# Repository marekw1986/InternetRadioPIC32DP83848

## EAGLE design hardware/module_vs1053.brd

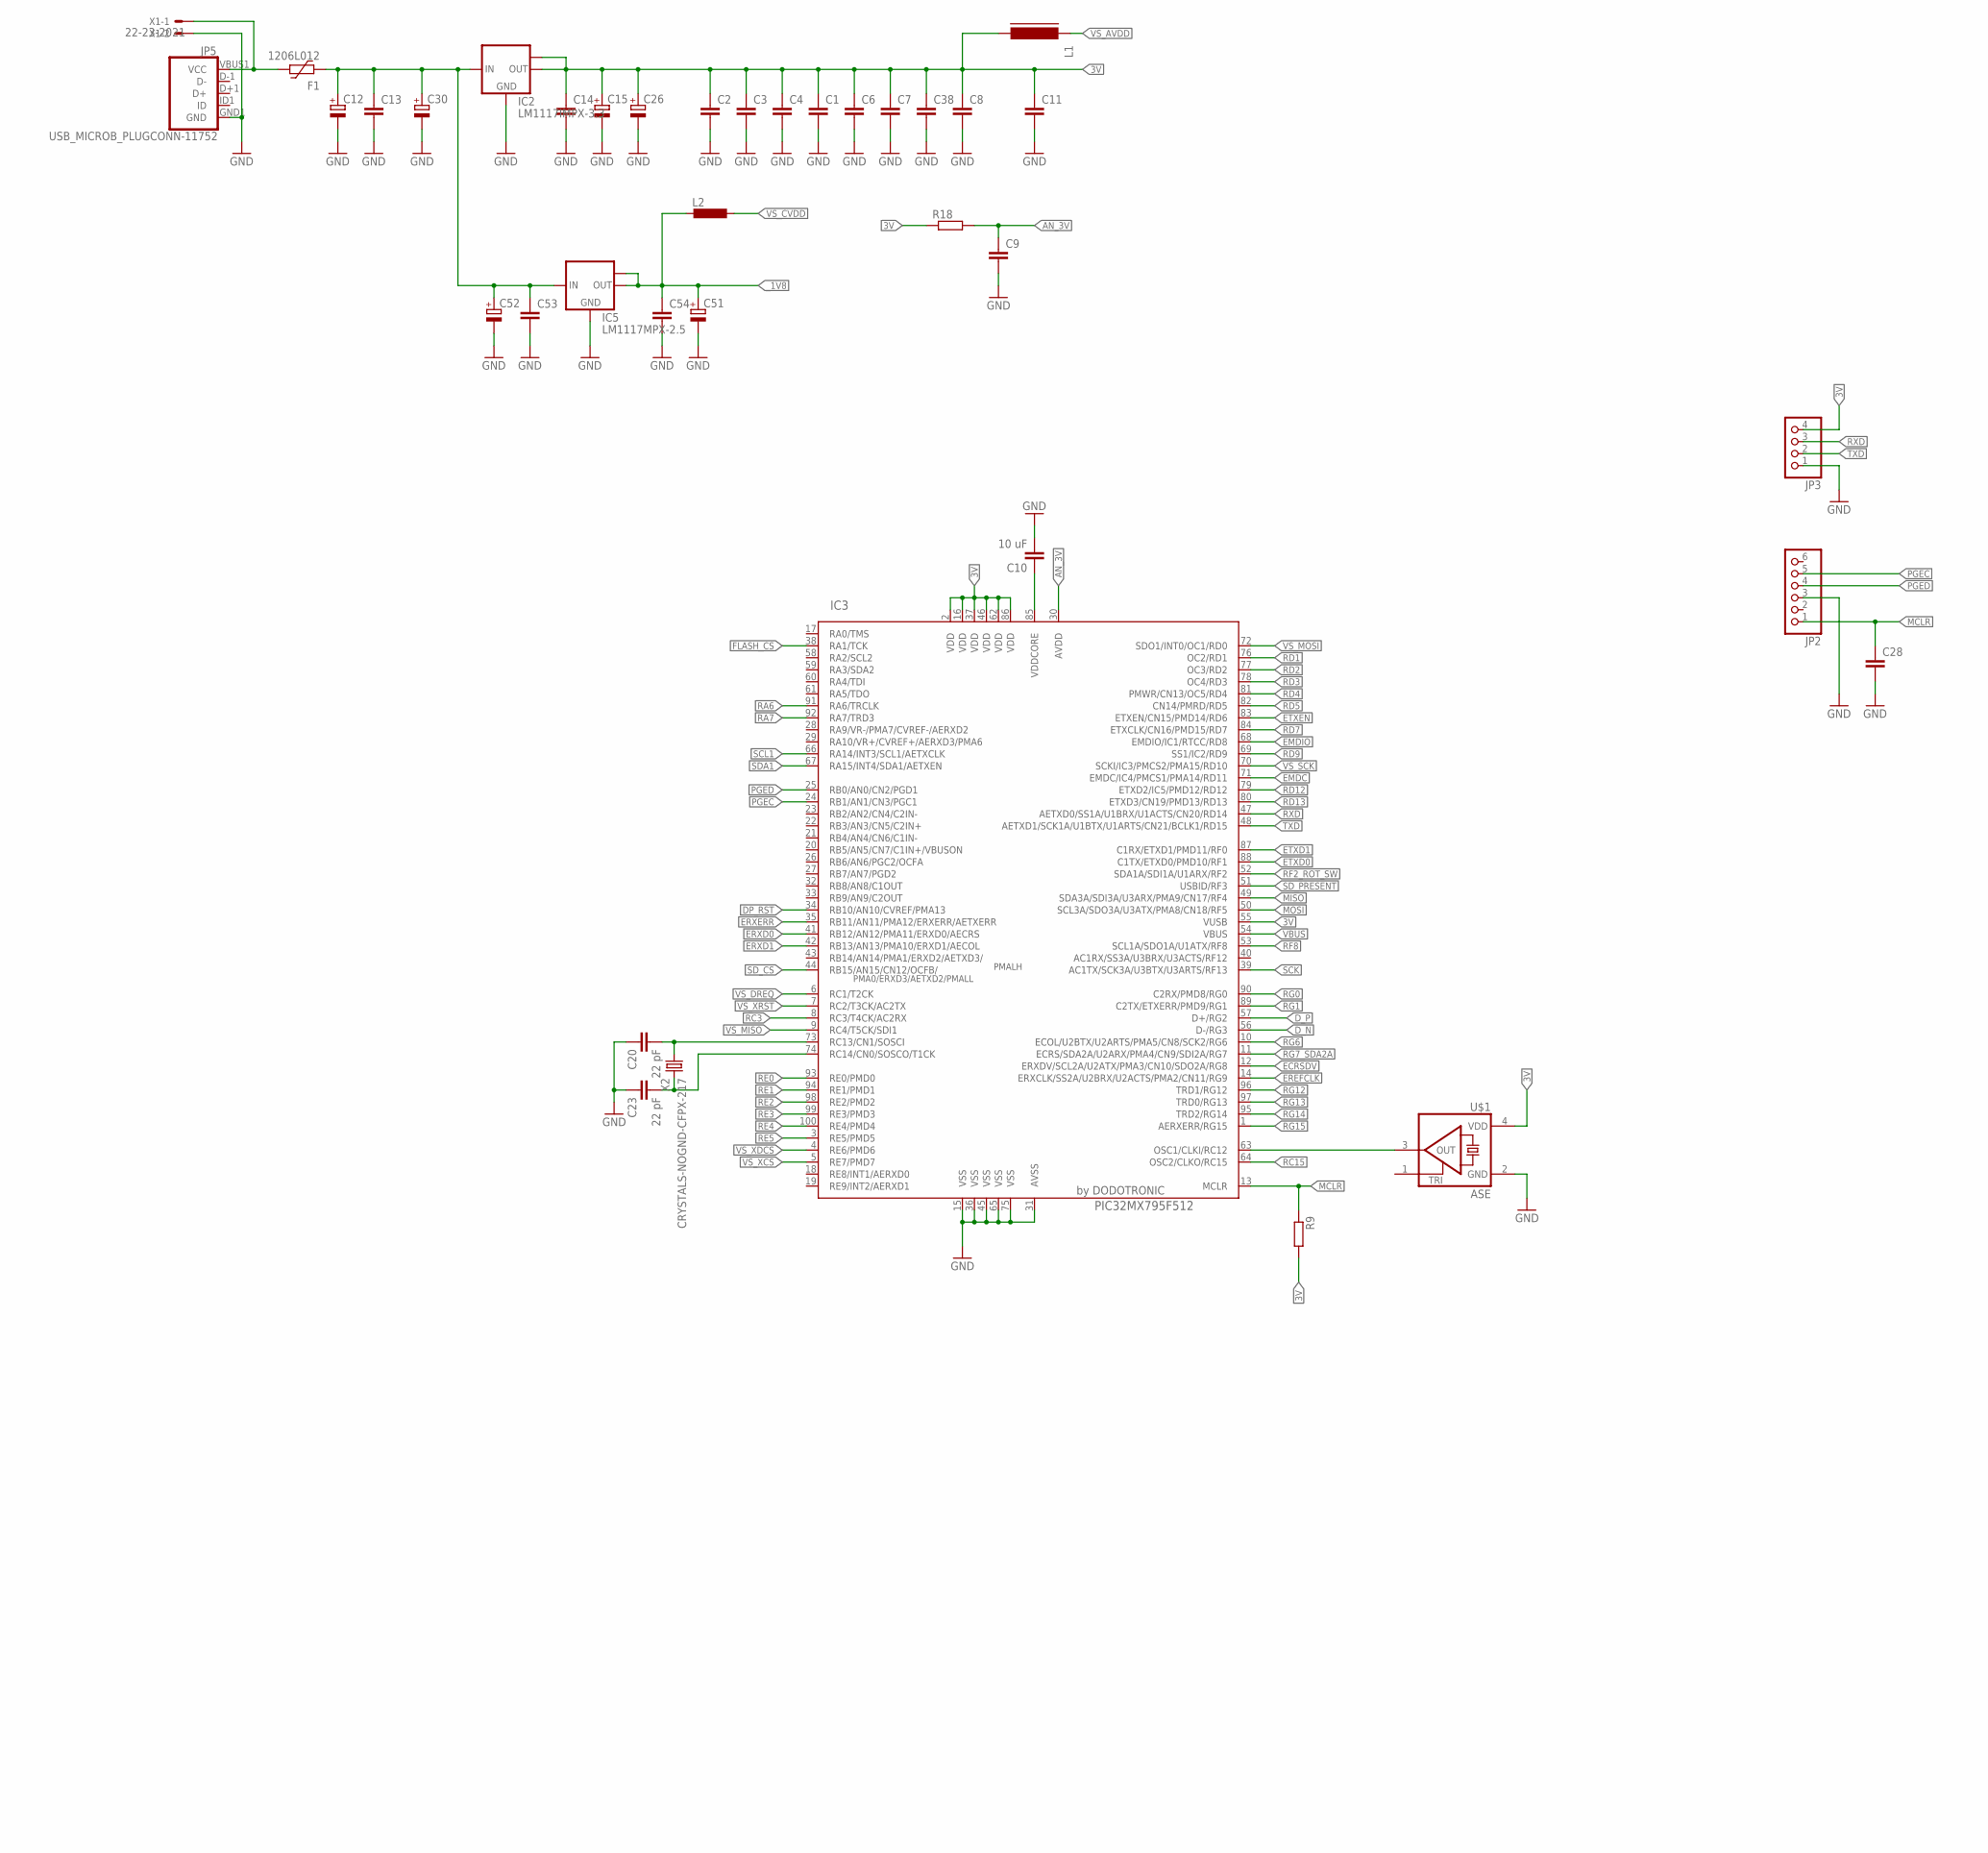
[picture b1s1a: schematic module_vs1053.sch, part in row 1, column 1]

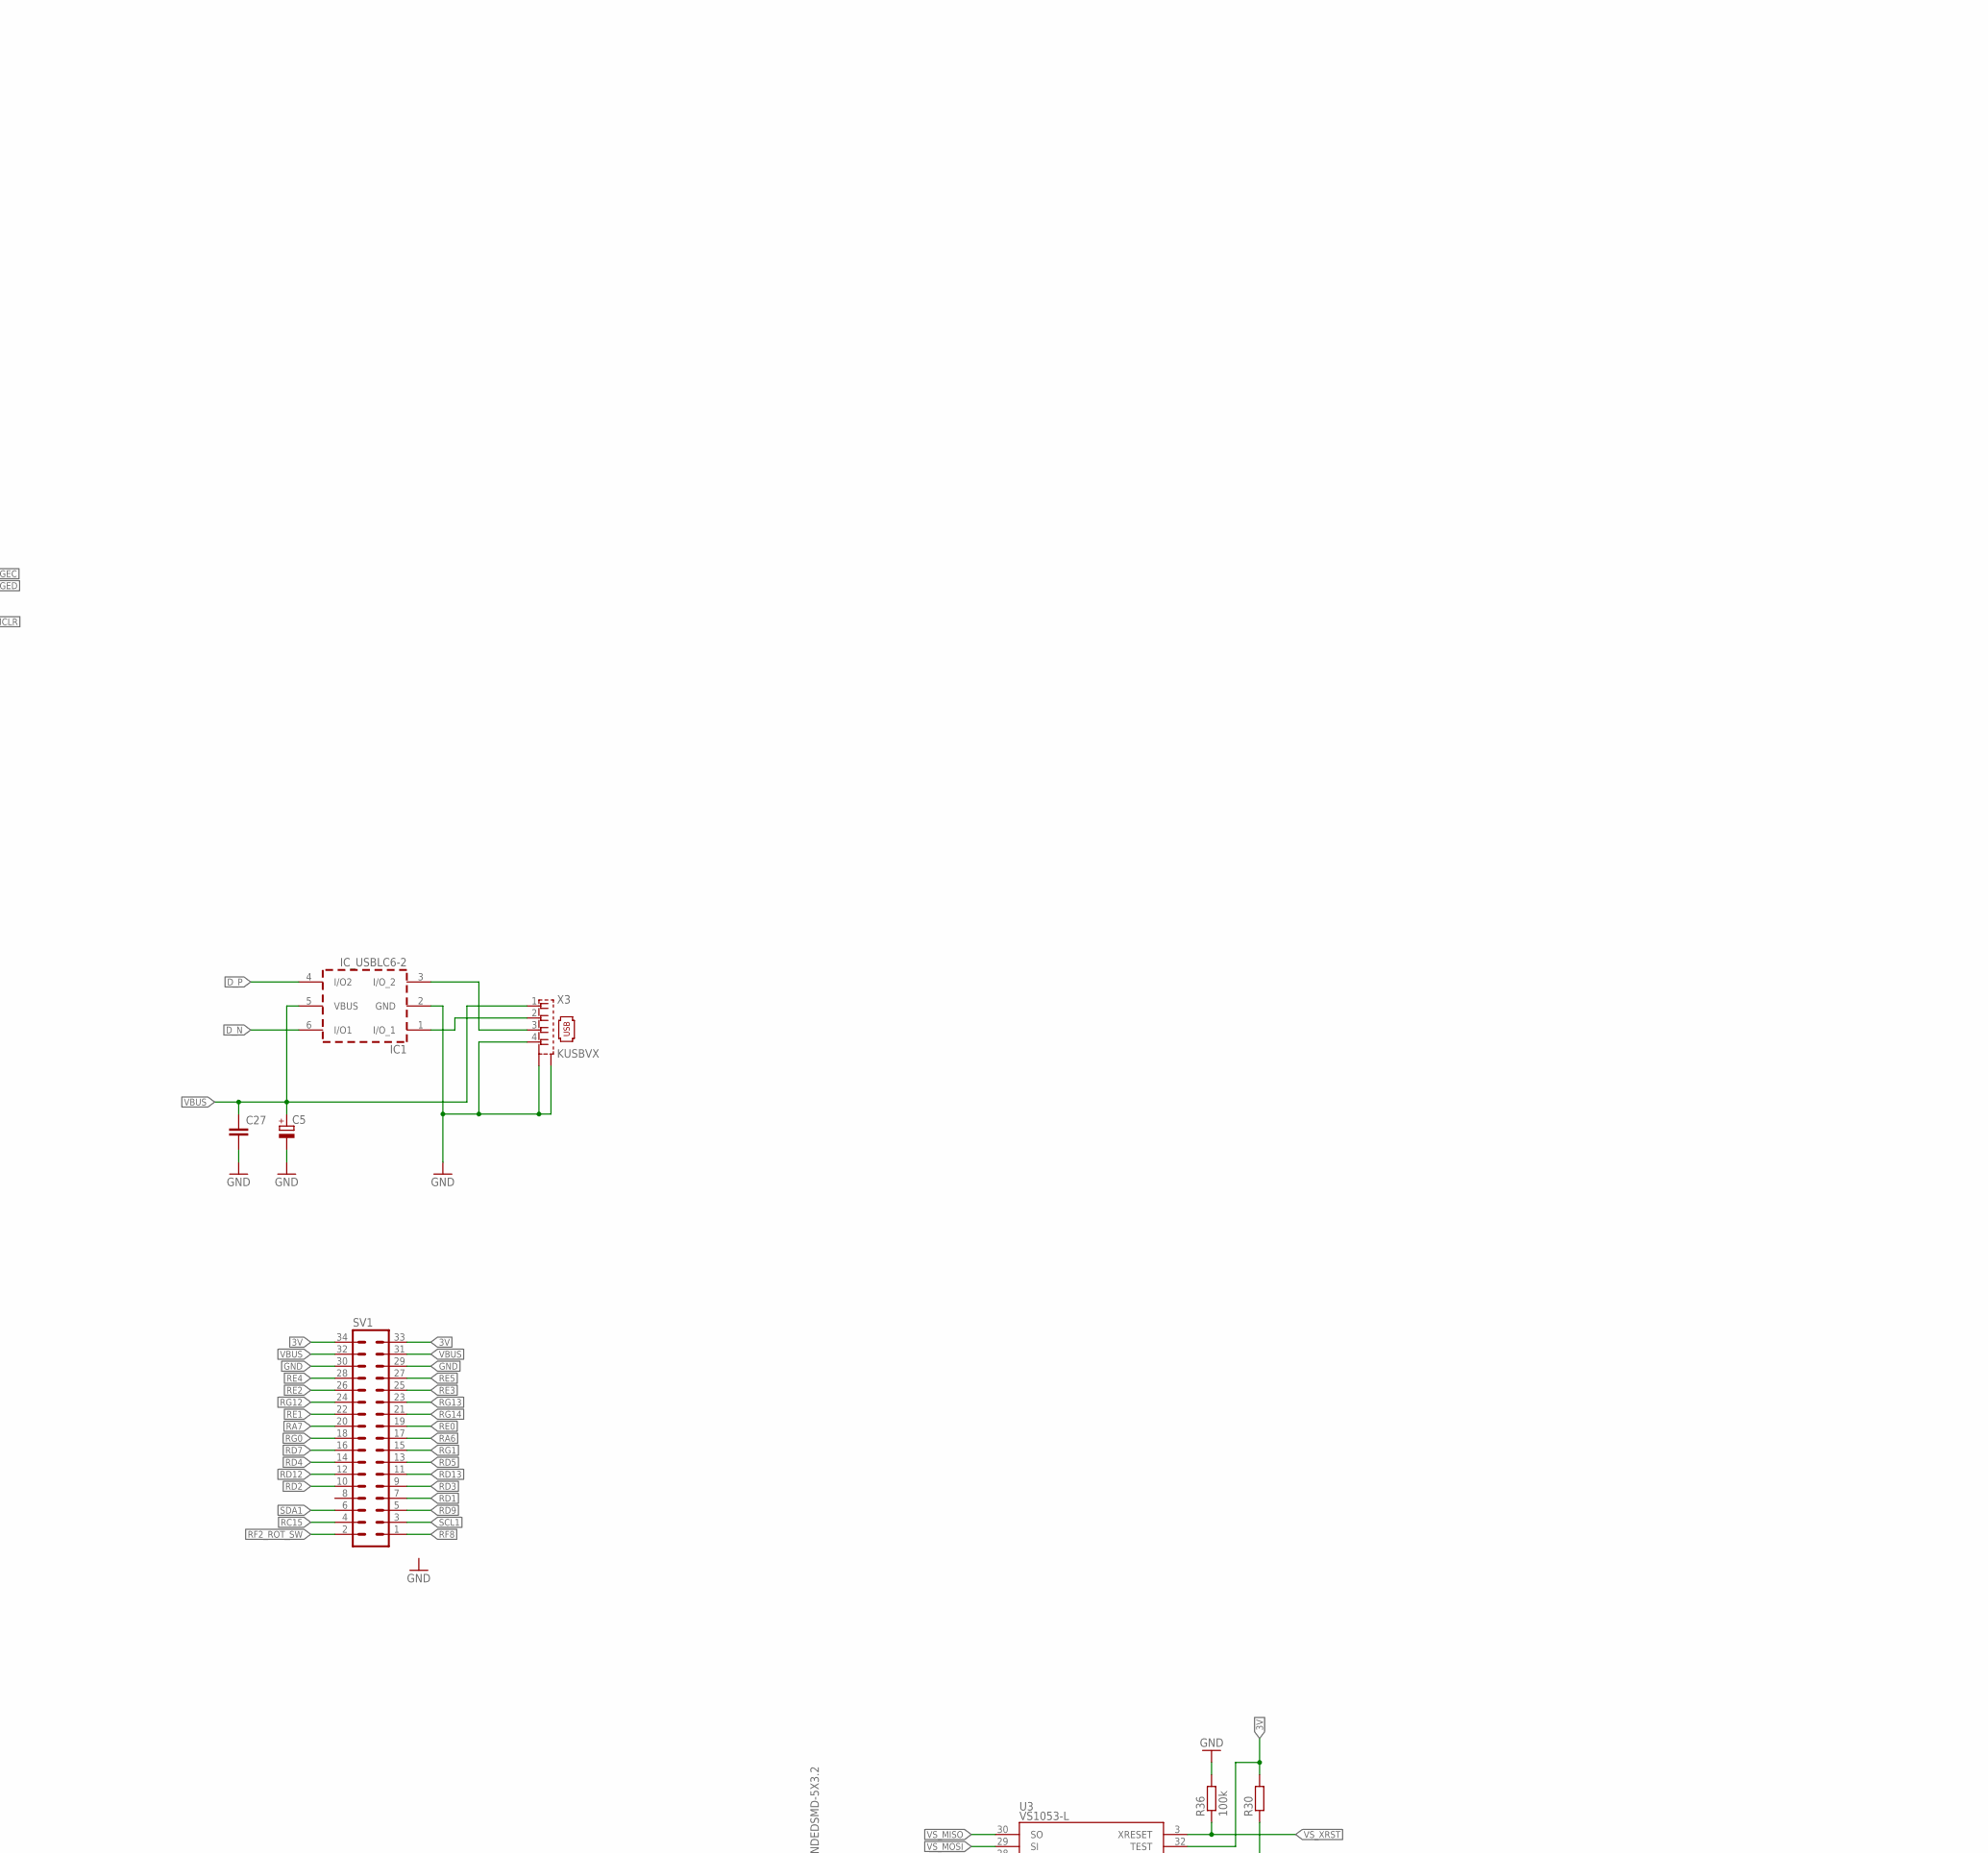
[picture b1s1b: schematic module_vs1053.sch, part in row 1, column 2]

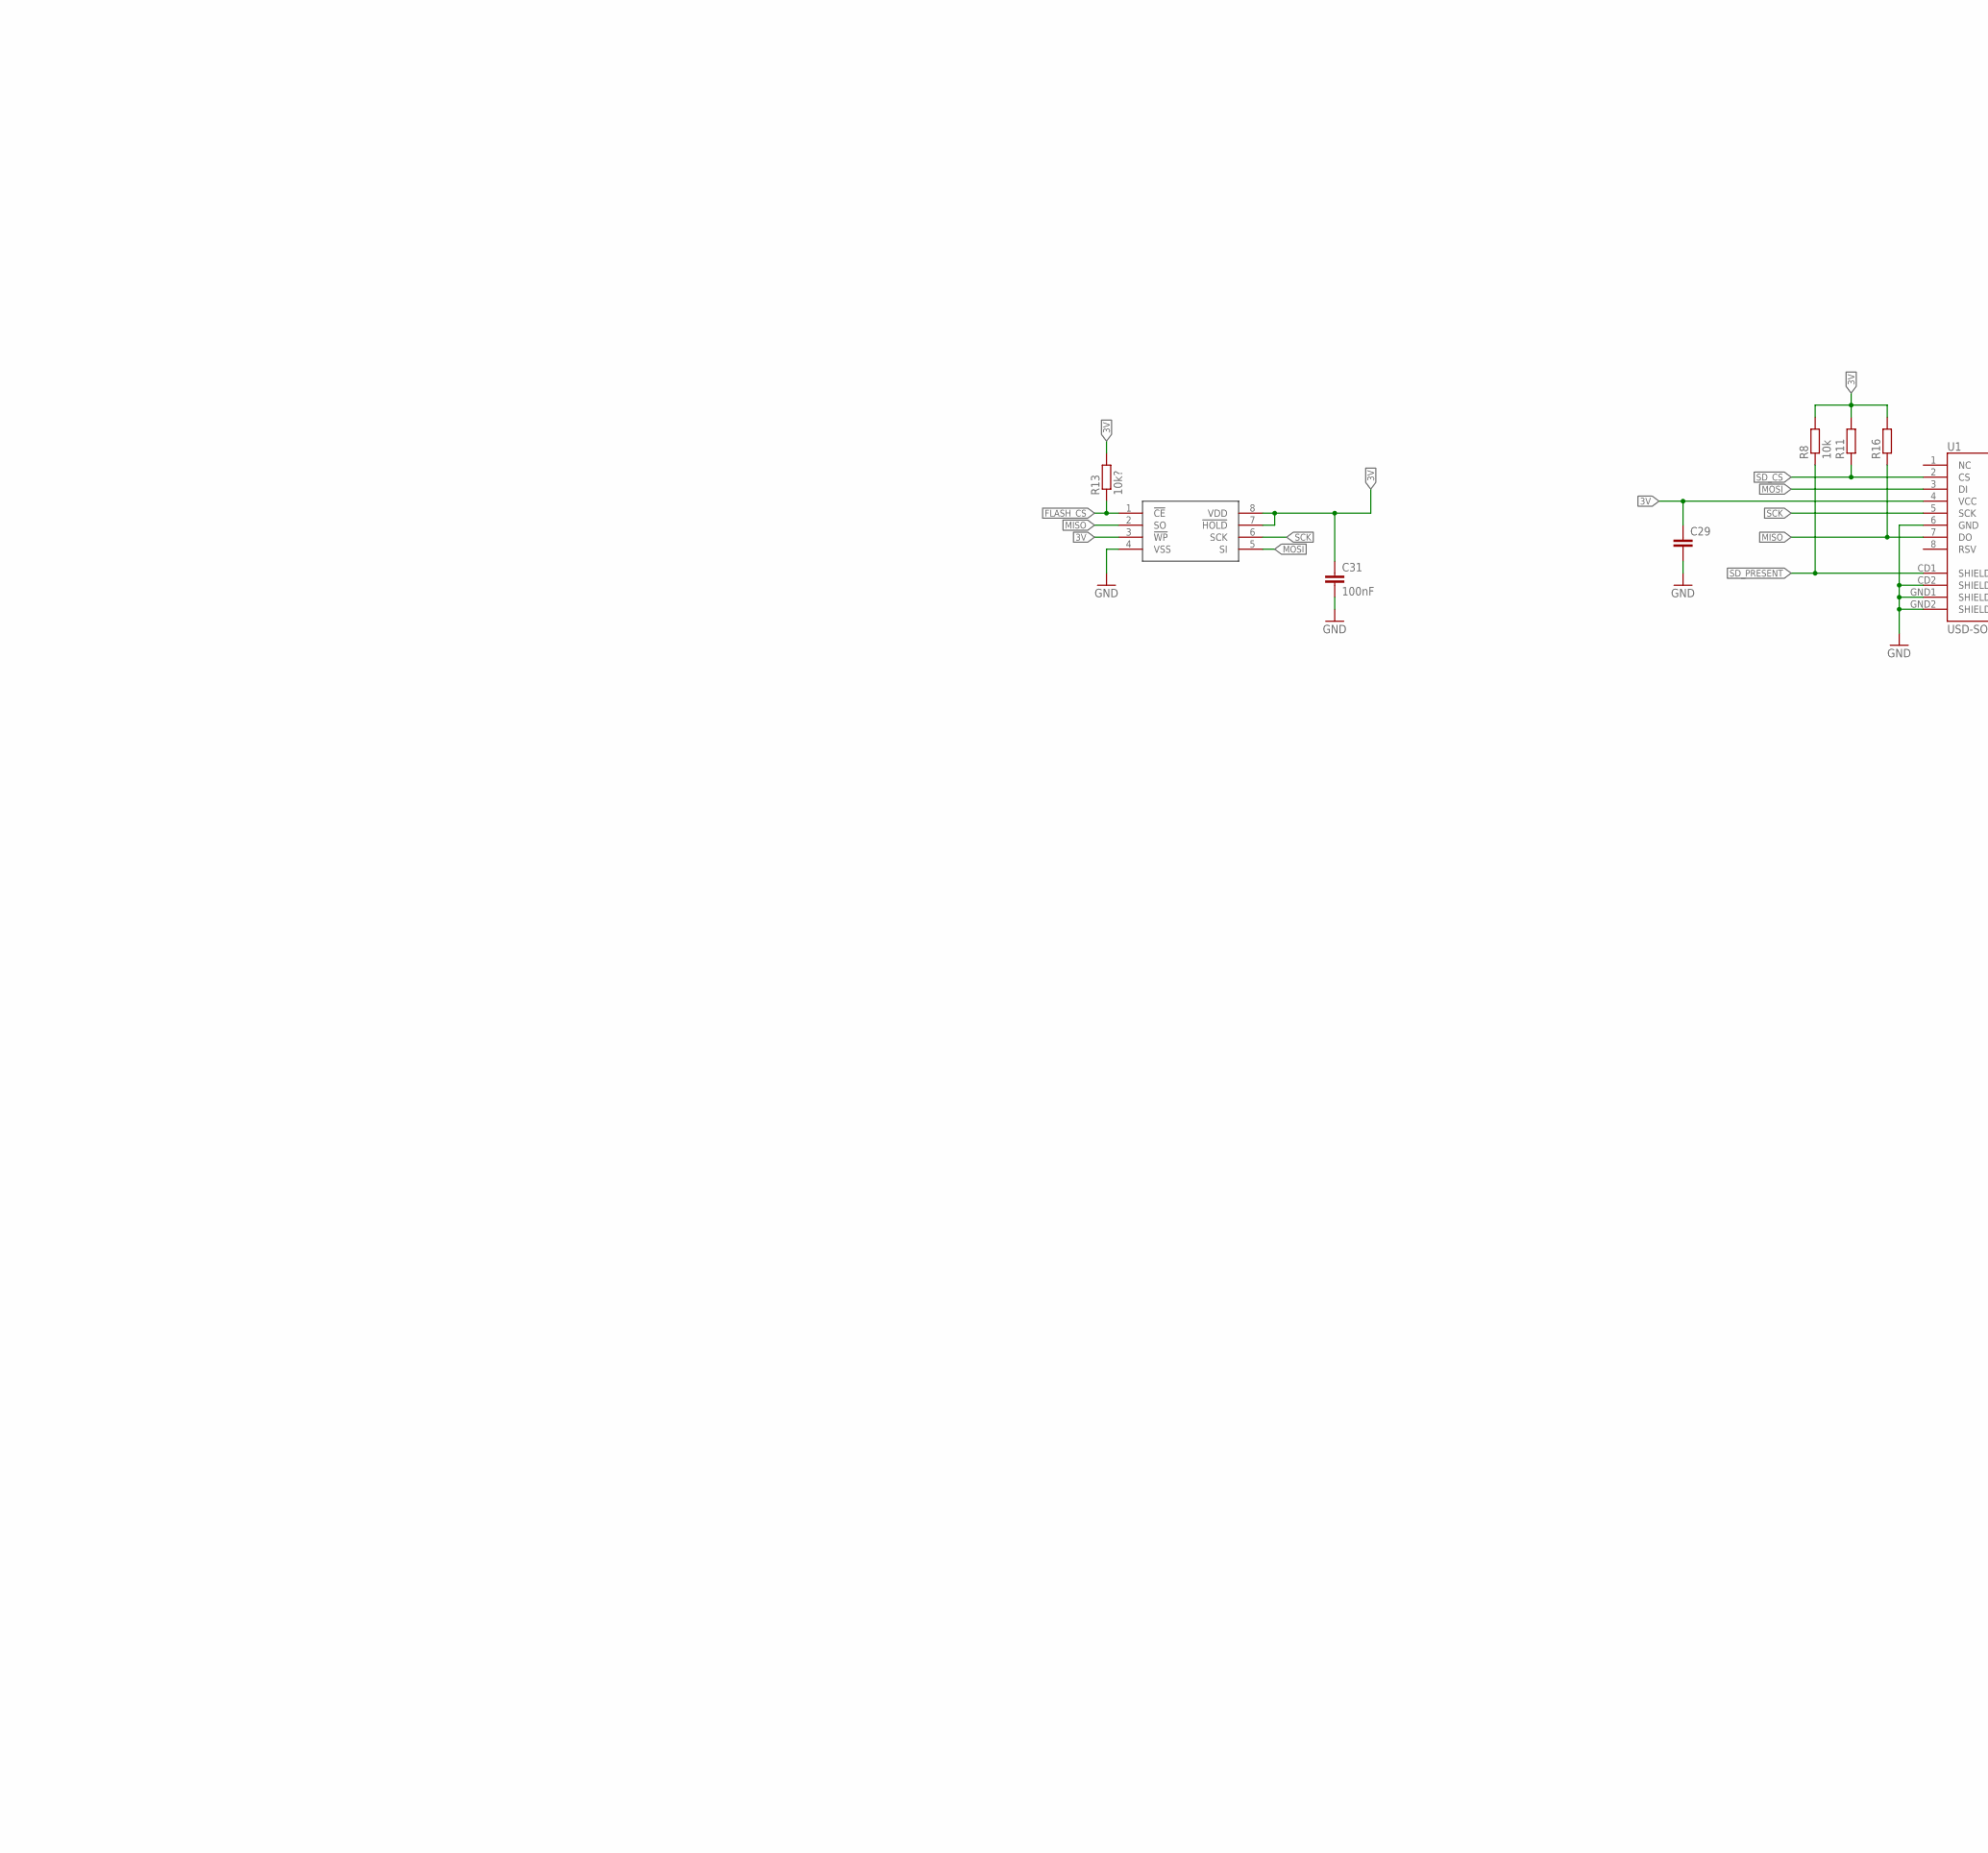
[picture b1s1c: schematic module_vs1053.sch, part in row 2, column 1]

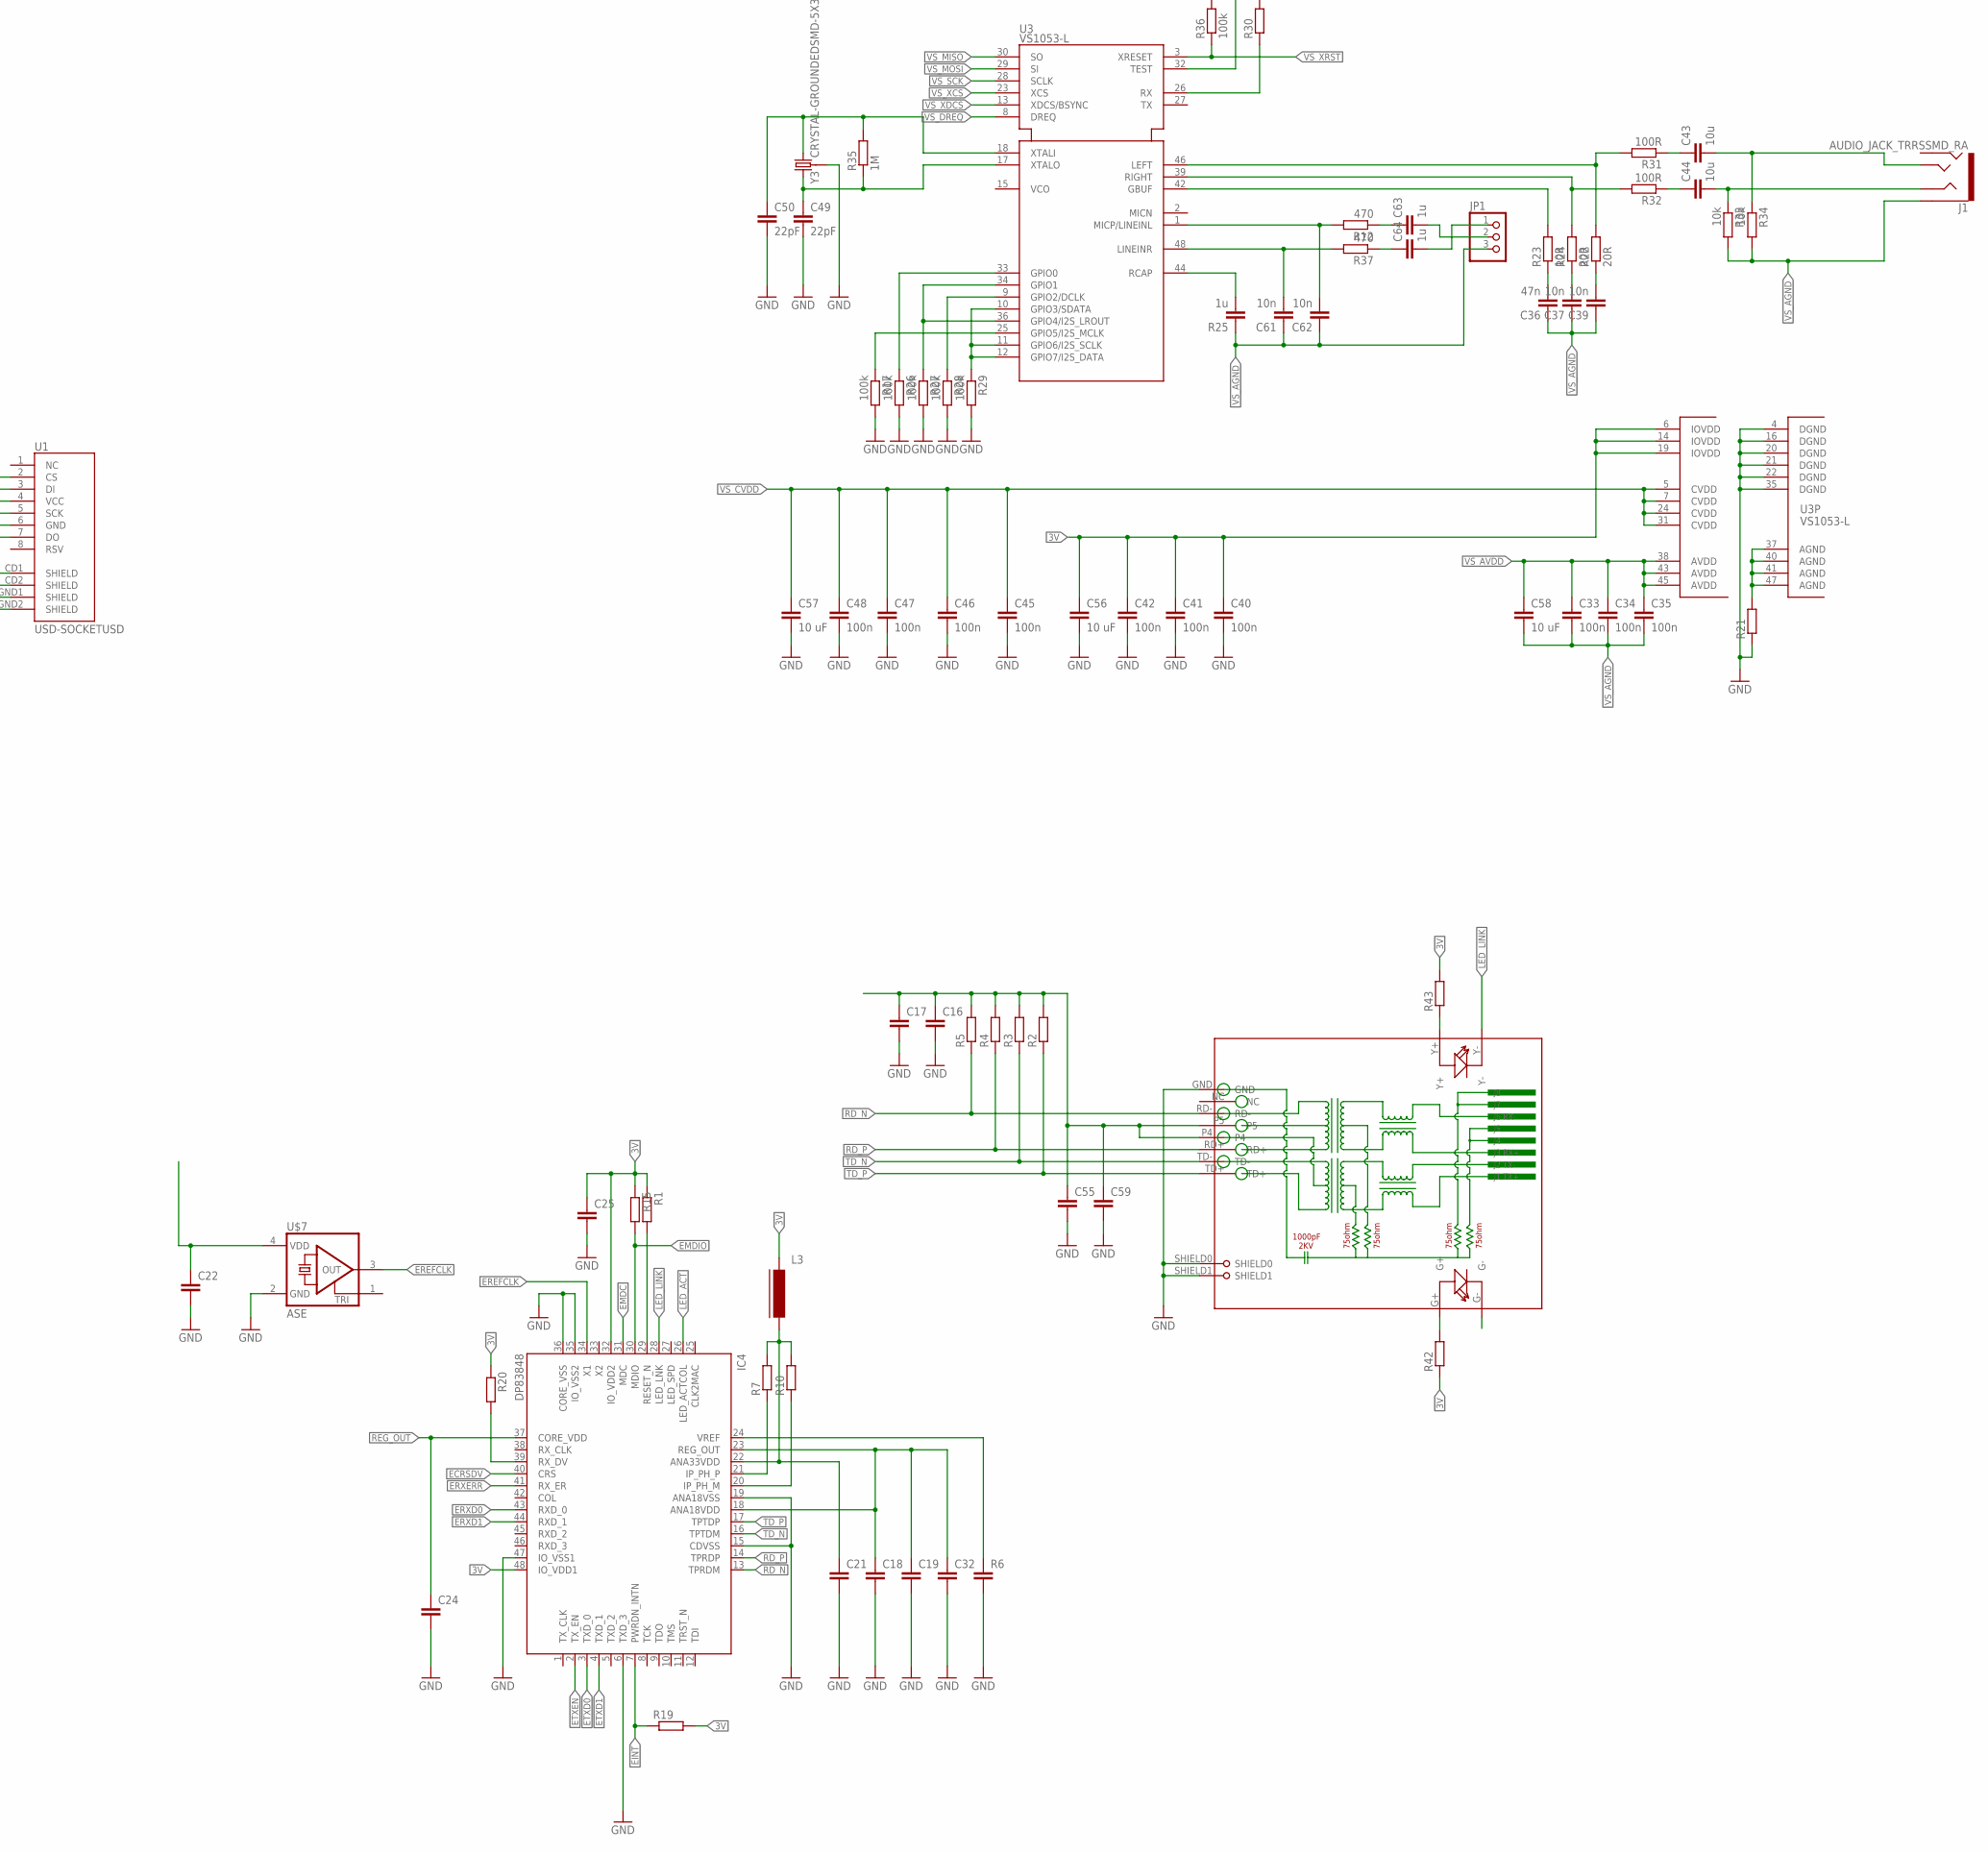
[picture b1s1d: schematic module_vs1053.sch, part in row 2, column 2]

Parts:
C1, C2, C3, C4, C6, C7, C8, C9, C11, C18, C19, C21, C22, C38: C-EUC0402; C0402
C5, C26, C30: CPOL-EUSMCA; SMC_A
C10, C56, C57, C58: 10 uF; C0603
C12, C15, C51, C52: CPOL-EUSMCB; SMC_B
C13, C14, C16, C17, C24, C25, C27, C28, C29, C32, C55, C59: C-EUC0603; C0603
C20, C23: 22 pF; C0603
C31: 100nF; C0603
C33, C34, C35, C46, C47, C48: 100n; C0603
C36: 47n; C0603
C37, C39, C61, C62: 10n; C0603
C40, C41, C42, C45: 100n; C0402
C43, C44: 10u; C0603
C49, C50: 22pF; C0603
C53, C54: C-EUC1206; C1206
C63, C64: 1u; C0603
F1: 1206L012; 1206L
IC1: IC_USBLC6-2; SOT-23-6L
IC2: LM1117IMPX-3.3; SOT223
IC3: PIC32MX795F512; TQFP100_12X12
IC4: DP83848; LQFP48
IC5: LM1117MPX-2.5; SOT223
J1: AUDIO_JACK_TRRSSMD_RA; AUDIO_JACK_3.5MM_TRRS_SMD_RA
JP1: PINHD-1X3; 1X03
JP2: PINHD-1X6; 1X06
JP3: PINHD-1X4; 1X04
JP5: USB_MICROB_PLUGCONN-11752; USB-B-MICRO-SMD_V03
L1, L3: FERRITE-0805; FB805
L2: L-EU0204/7; 0204/7
R1, R7, R10, R19: R-EU_R0402; R0402
R2, R3, R4, R5, R9, R11, R15, R16, R20, R21, R42, R43: R-EU_R0603; R0603
R6: C-EUC0603; C0603
R8, R33, R34: 10k; R0603
R12, R37: 470; 0204/7
R13: 10k?; R0603
R17, R26, R27, R28, R29: 100k; R0402
R18: R-EU_R0805; R0805
R22, R24: 20R; R0603
R23: 10R; R0603
R25: 1u; C0603
R30: R-EU_0204/7; 0204/7
R31, R32: 100R; R0603
R35: 1M; R0603
R36: 100k; R0603
RJ1: HR911105A
SV1: ML34L
U1: USD-SOCKETUSD; USD-SOCKET-PP
U3: VS1053-L; LQFP48
U$1, U$7: ASE
U$2: SST25VF016BSO8M; SO-08M
X1: 22-23-2021
X2: CRYSTALS-NOGND-CFPX-217; 3.2X1.5-2-PAD
X3: KUSBVX
Y3: CRYSTAL-GROUNDEDSMD-5X3.2; CRYSTAL-SMD-5X3.2-4PAD

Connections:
3V: C1.1, C2.1, C3.1, C4.1, C6.1, C7.1, C8.1, C11.1, C14.1, C15.+, C22.1, C25.1, C26.+, C29.1, C31.1, C38.1, C40.1, C41.1, C42.1, C56.1, IC2.2 (OUT), IC2.TAB (OUT1), IC3.2 (VDD), IC3.16 (VDD), IC3.37 (VDD), IC3.46 (VDD), IC3.55 (VUSB), IC3.62 (VDD), IC3.86 (VDD), IC4.32 (IO_VDD2), IC4.48 (IO_VDD1), JP3.4, L1.2, L3.1, R1.1, R8.2, R9.2, R11.2, R13.2, R15.1, R16.2, R18.1, R19.2, R20.1, R30.2, R42.1, R43.2, SV1.33, SV1.34, U1.4 (VCC), U3.6 (IOVDD), U3.14 (IOVDD), U3.19 (IOVDD), U3.32 (TEST), U$1.4 (VDD), U$2.3 (!WP), U$2.7 (!HOLD), U$2.8 (VDD), U$7.4 (VDD)
A3V: C16.1, C17.1, C21.1, C55.1, C59.1, IC4.22 (ANA33VDD), L3.2, R2.2, R3.2, R4.2, R5.2, R7.2, R10.2, RJ1.P4, RJ1.P5
AN_3V: C9.1, IC3.30 (AVDD), R18.2
D2_N: IC1.1 (I/O_1), X3.2
D2_P: IC1.3 (I/O_2), X3.3
DP_RST: IC3.34 (RB10/AN10/CVREF/PMA13), IC4.29 (RESET_N), R1.2
D_N: IC1.6 (I/O1), IC3.56 (D-/RG3)
D_P: IC1.4 (I/O2), IC3.57 (D+/RG2)
ECRSDV: IC3.12 (ERXDV/SCL2A/U2ATX/PMA3/CN10/SDO2A/RG8), IC4.40 (CRS)
EINT: IC4.7 (PWRDN_INTN), R19.1
EMDC: IC3.71 (EMDC/IC4/PMCS1/PMA14/RD11), IC4.31 (MDC)
EMDIO: IC3.68 (EMDIO/IC1/RTCC/RD8), IC4.30 (MDIO), R15.2
EREFCLK: IC3.14 (ERXCLK/SS2A/U2BRX/U2ACTS/PMA2/CN11/RG9), IC4.34 (X1), U$7.3 (OUT)
ERXD0: IC3.41 (RB12/AN12/PMA11/ERXD0/AECRS), IC4.43 (RXD_0)
ERXD1: IC3.42 (RB13/AN13/PMA10/ERXD1/AECOL), IC4.44 (RXD_1)
ERXERR: IC3.35 (RB11/AN11/PMA12/ERXERR/AETXERR), IC4.41 (RX_ER)
ETXD0: IC3.88 (C1TX/ETXD0/PMD10/RF1), IC4.3 (TXD_0)
ETXD1: IC3.87 (C1RX/ETXD1/PMD11/RF0), IC4.4 (TXD_1)
ETXEN: IC3.83 (ETXEN/CN15/PMD14/RD6), IC4.2 (TX_EN)
FLASH_CS: IC3.38 (RA1/TCK), R13.1, U$2.1 (!CE)
GND: C1.2, C2.2, C3.2, C4.2, C5.-, C6.2, C7.2, C8.2, C9.2, C10.2, C11.2, C12.-, C13.2, C14.2, C15.-, C16.2, C17.2, C18.2, C19.2, C20.1, C21.2, C22.2, C23.1, C24.2, C25.2, C26.-, C27.2, C28.2, C29.2, C30.-, C31.2, C32.2, C38.2, C40.2, C41.2, C42.2, C45.2, C46.2, C47.2, C48.2, C49.2, C50.2, C51.-, C52.-, C53.2, C54.2, C55.2, C56.2, C57.2, C59.2, IC1.2 (GND), IC2.1 (GND), IC3.15 (VSS), IC3.31 (AVSS), IC3.36 (VSS), IC3.45 (VSS), IC3.65 (VSS), IC3.75 (VSS), IC4.6 (TXD_3), IC4.15 (CDVSS), IC4.19 (ANA18VSS), IC4.35 (IO_VSS2), IC4.36 (CORE_VSS), IC4.47 (IO_VSS1), IC5.1 (GND), JP2.3, JP3.1, JP5.GND1 (GND), R6.2, R17.2, R21.1, R26.2, R27.2, R28.2, R29.2, R36.2, RJ1.GND, RJ1.SHIELD0, RJ1.SHIELD1, SV1.29, SV1.30, U1.6 (GND), U1.CD2 (SHIELD), U1.GND1 (SHIELD), U1.GND2 (SHIELD), U3.4 (DGND), U3.16 (DGND), U3.20 (DGND), U3.21 (DGND), U3.22 (DGND), U3.35 (DGND), U$1.2 (GND), U$2.4 (VSS), U$7.2 (GND), X1.2, X3.4, X3.M1 (S1), X3.M2 (S2), Y3.2 (3), Y3.4 (3)
IN_LEFT: C63.2, JP1.2
IN_RIGHT: C64.2, JP1.1
LED_ACT: IC4.26 (LED_ACTCOL), RJ1.G-
LED_LINK: IC4.28 (LED_LNK), RJ1.Y-
MCLR: C28.1, IC3.13 (MCLR), JP2.1, R9.1
MISO: IC3.49 (SDA3A/SDI3A/U3ARX/PMA9/CN17/RF4), R16.1, U1.7 (DO), U$2.2 (SO)
MOSI: IC3.50 (SCL3A/SDO3A/U3ATX/PMA8/CN18/RF5), U1.3 (DI), U$2.5 (SI)
unnamed: IC4.21 (IP_PH_P), R7.1
unnamed: R17.1, U3.25 (GPIO5/I2S_MCLK)
unnamed: IC4.24 (VREF), R6.1
unnamed: C61.2, R37.2, U3.48 (LINEINR)
unnamed: IC4.20 (IP_PH_M), R10.1
unnamed: C10.1, IC3.85 (VDDCORE)
unnamed: R42.2, RJ1.G+
unnamed: C62.2, R12.2, U3.1 (MICP/LINEINL)
unnamed: C64.1, R37.1
unnamed: C63.1, R12.1
unnamed: F1.1, JP5.VBUS1 (VCC), X1.1
unnamed: C36.2, R23.1
unnamed: R43.1, RJ1.Y+
PGEC: IC3.24 (RB1/AN1/CN3/PGC1), JP2.5
PGED: IC3.25 (RB0/AN0/CN2/PGD1), JP2.4
PH0: IC3.63 (OSC1/CLKI/RC12), U$1.3 (OUT)
RA6: IC3.91 (RA6/TRCLK), SV1.17
RA7: IC3.92 (RA7/TRD3), SV1.20
RC3: IC3.8 (RC3/T4CK/AC2RX)
RC15: IC3.64 (OSC2/CLKO/RC15), SV1.4
RD1: IC3.76 (OC2/RD1), SV1.7
RD2: IC3.77 (OC3/RD2), SV1.10
RD3: IC3.78 (OC4/RD3), SV1.9
RD4: IC3.81 (PMWR/CN13/OC5/RD4), SV1.14
RD5: IC3.82 (CN14/PMRD/RD5), SV1.13
RD7: IC3.84 (ETXCLK/CN16/PMD15/RD7), SV1.16
RD9: IC3.69 (SS1/IC2/RD9), SV1.5
RD12: IC3.79 (ETXD2/IC5/PMD12/RD12), SV1.12
RD13: IC3.80 (ETXD3/CN19/PMD13/RD13), SV1.11
RD_N: IC4.13 (TPRDM), R5.1, RJ1.RD-
RD_P: IC4.14 (TPRDP), R4.1, RJ1.RD+
RE0: IC3.93 (RE0/PMD0), SV1.19
RE1: IC3.94 (RE1/PMD1), SV1.22
RE2: IC3.98 (RE2/PMD2), SV1.26
RE3: IC3.99 (RE3/PMD3), SV1.25
RE4: IC3.100 (RE4/PMD4), SV1.28
RE5: IC3.3 (RE5/PMD5), SV1.27
REG_OUT: C18.1, C19.1, C24.1, C32.1, IC4.18 (ANA18VDD), IC4.23 (REG_OUT), IC4.37 (CORE_VDD)
RF2_ROT_SW: IC3.52 (SDA1A/SDI1A/U1ARX/RF2), SV1.2
RF8: IC3.53 (SCL1A/SDO1A/U1ATX/RF8), SV1.1
RG0: IC3.90 (C2RX/PMD8/RG0), SV1.18
RG1: IC3.89 (C2TX/ETXERR/PMD9/RG1), SV1.15
RG6: IC3.10 (ECOL/U2BTX/U2ARTS/PMA5/CN8/SCK2/RG6)
RG7_SDA2A: IC3.11 (ECRS/SDA2A/U2ARX/PMA4/CN9/SDI2A/RG7)
RG12: IC3.96 (TRD1/RG12), SV1.24
RG13: IC3.97 (TRD0/RG13), SV1.23
RG14: IC3.95 (TRD2/RG14), SV1.21
RG15: IC3.1 (AERXERR/RG15)
RXD: IC3.47 (AETXD0/SS1A/U1BRX/U1ACTS/CN20/RD14), JP3.3
RX_DV: IC4.39 (RX_DV), R20.2
SCK: IC3.39 (AC1TX/SCK3A/U3BTX/U3ARTS/RF13), U1.5 (SCK), U$2.6 (SCK)
SCL1: IC3.66 (RA14/INT3/SCL1/AETXCLK), SV1.3
SDA1: IC3.67 (RA15/INT4/SDA1/AETXEN), SV1.6
SD_CS: IC3.44 (RB15/AN15/CN12/OCFB/), R11.1, U1.2 (CS)
SD_PRESENT: IC3.51 (USBID/RF3), R8.1, U1.CD1 (SHIELD)
SOSCI: C20.2, IC3.73 (RC13/CN1/SOSCI), X2.1
SOSCO: C23.2, IC3.74 (RC14/CN0/SOSCO/T1CK), X2.2
TD_N: IC4.16 (TPTDM), R3.1, RJ1.TD-
TD_P: IC4.17 (TPTDP), R2.1, RJ1.TD+
TXD: IC3.48 (AETXD1/SCK1A/U1BTX/U1ARTS/CN21/BCLK1/RD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), JP3.2
VBUS: C5.+, C12.+, C13.1, C27.1, C30.+, C52.+, C53.1, F1.2, IC1.5 (VBUS), IC2.3 (IN), IC3.54 (VBUS), IC5.3 (IN), SV1.31, SV1.32, X3.1
VS_AGND: C33.2, C34.2, C35.2, C36.1, C37.1, C39.1, C58.2, C61.1, C62.1, J1.EARTH, JP1.3, R21.2, R25.1, R33.2, R34.2, U3.37 (AGND), U3.40 (AGND), U3.41 (AGND), U3.47 (AGND)
VS_AVDD: C33.1, C34.1, C35.1, C58.1, L1.1, U3.38 (AVDD), U3.43 (AVDD), U3.45 (AVDD)
VS_CVDD: C45.1, C46.1, C47.1, C48.1, C57.1, L2.1, U3.5 (CVDD), U3.7 (CVDD), U3.24 (CVDD), U3.31 (CVDD)
VS_DREQ: IC3.6 (RC1/T2CK), U3.8 (DREQ)
VS_MISO: IC3.9 (RC4/T5CK/SDI1), U3.30 (SO)
VS_MOSI: IC3.72 (SDO1/INT0/OC1/RD0), U3.29 (SI)
VS_N$9: C50.1, R35.2, U3.18 (XTALI), Y3.1 (2)
VS_N$13: C49.1, R35.1, U3.17 (XTALO), Y3.3 (1)
VS_N$14: R22.2, R31.2, U3.46 (LEFT)
VS_N$15: R23.2, U3.42 (GBUF)
VS_N$16: R24.2, R32.2, U3.39 (RIGHT)
VS_N$17: R25.2, U3.44 (RCAP)
VS_N$24: C37.2, R24.1
VS_N$25: C39.2, R22.1
VS_N$26: R29.1, U3.10 (GPIO3/SDATA), U3.11 (GPIO6/I2S_SCLK), U3.12 (GPIO7/I2S_DATA)
VS_N$27: R28.1, U3.9 (GPIO2/DCLK)
VS_N$28: R27.1, U3.34 (GPIO1), U3.36 (GPIO4/I2S_LROUT)
VS_N$30: R26.1, U3.33 (GPIO0)
VS_N$34: R30.1, U3.26 (RX)
VS_N$35: C43.1, R31.1
VS_N$36: C44.1, R32.1
VS_N$37: C44.2, J1.RING1, R33.1
VS_N$38: C43.2, J1.TIP, R34.1
VS_SCK: IC3.70 (SCKI/IC3/PMCS2/PMA15/RD10), U3.28 (SCLK)
VS_XCS: IC3.5 (RE7/PMD7), U3.23 (XCS)
VS_XDCS: IC3.4 (RE6/PMD6), U3.13 (XDCS/BSYNC)
VS_XRST: IC3.7 (RC2/T3CK/AC2TX), R36.1, U3.3 (XRESET)
_1V8: C51.+, C54.1, IC5.2 (OUT), IC5.TAB (OUT1), L2.2

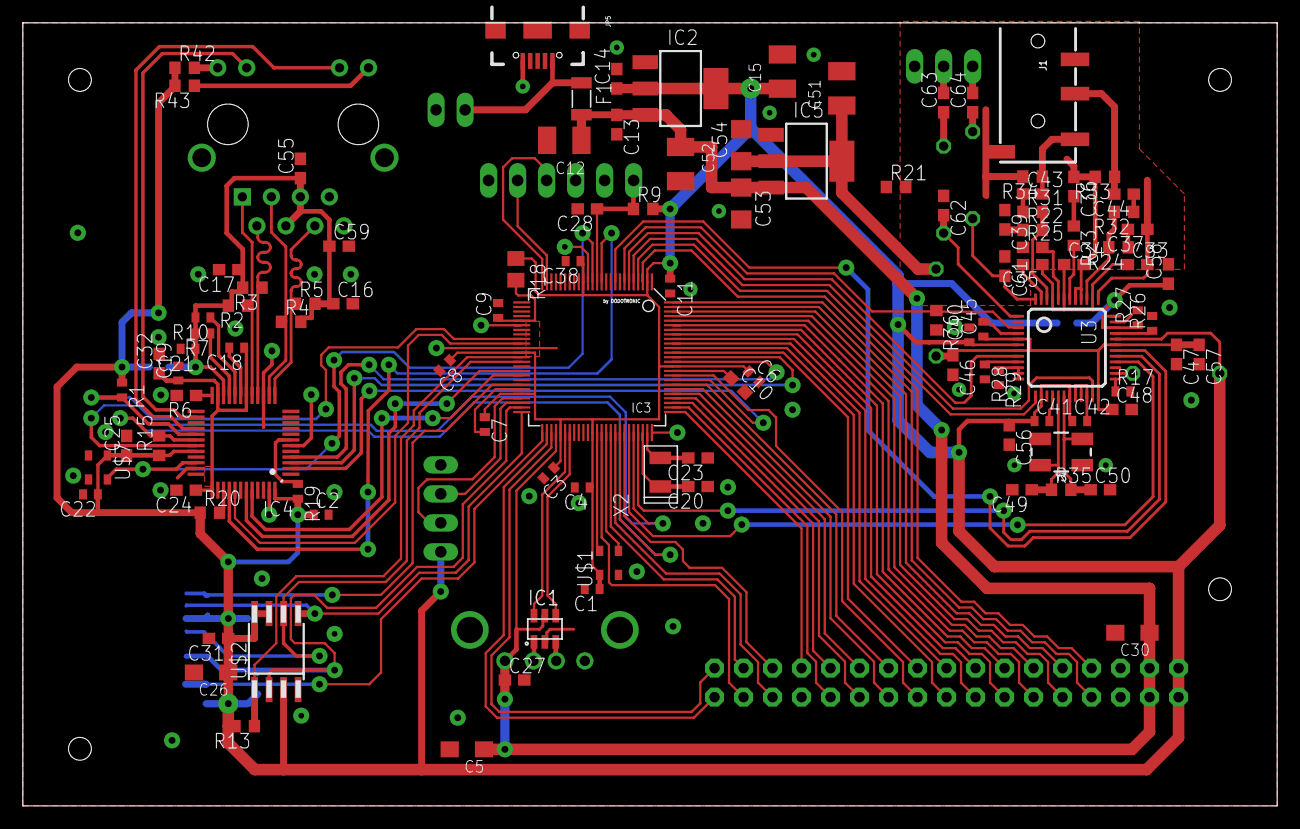
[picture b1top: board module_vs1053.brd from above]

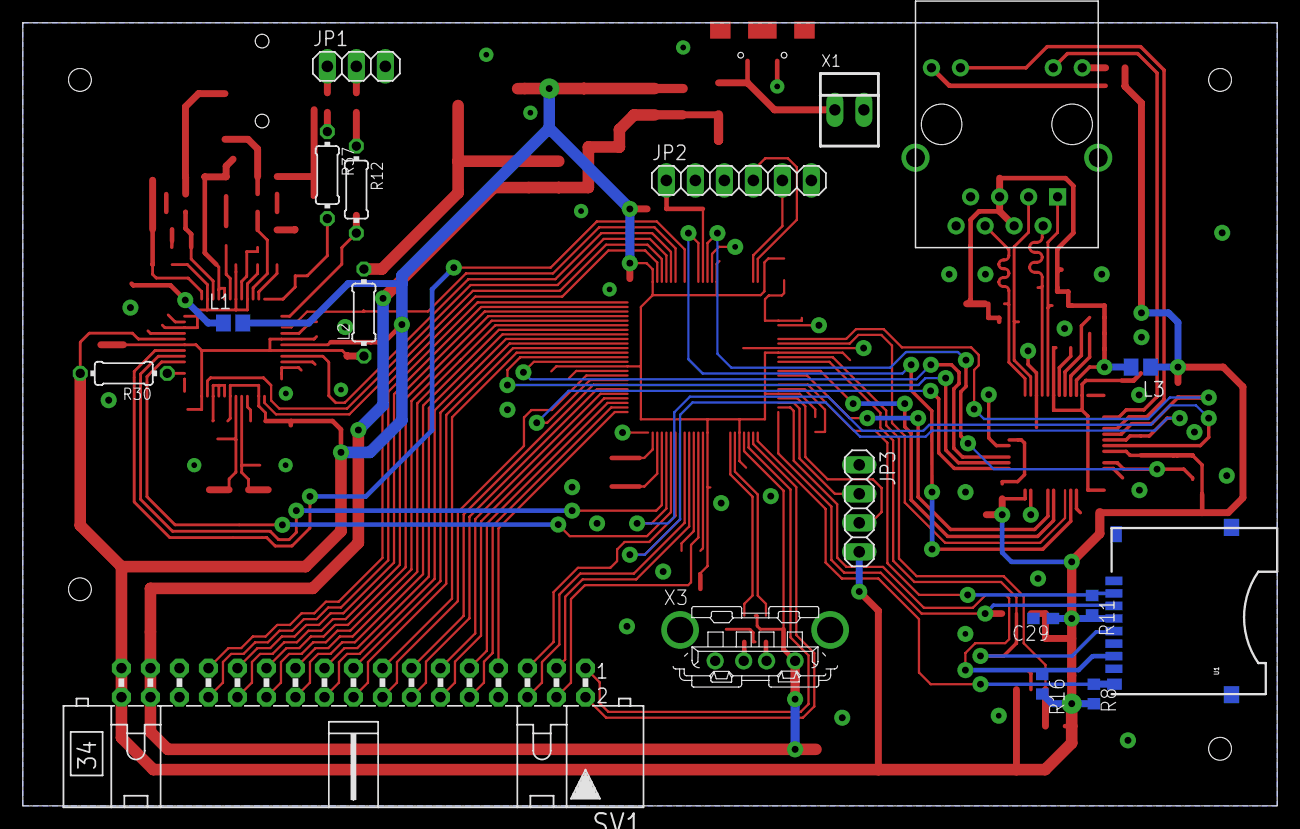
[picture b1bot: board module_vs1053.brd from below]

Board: 2 copper layers, 109.9 x 68.6 mm, 126 parts (18 on the bottom side), 113 nets.

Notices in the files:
parts and their libraries:
SparkFun-Electromechanical: Licensing: Creative Commons ShareAlike 4.0 International - https://creativecommons.org/licenses/by-sa/4.0
